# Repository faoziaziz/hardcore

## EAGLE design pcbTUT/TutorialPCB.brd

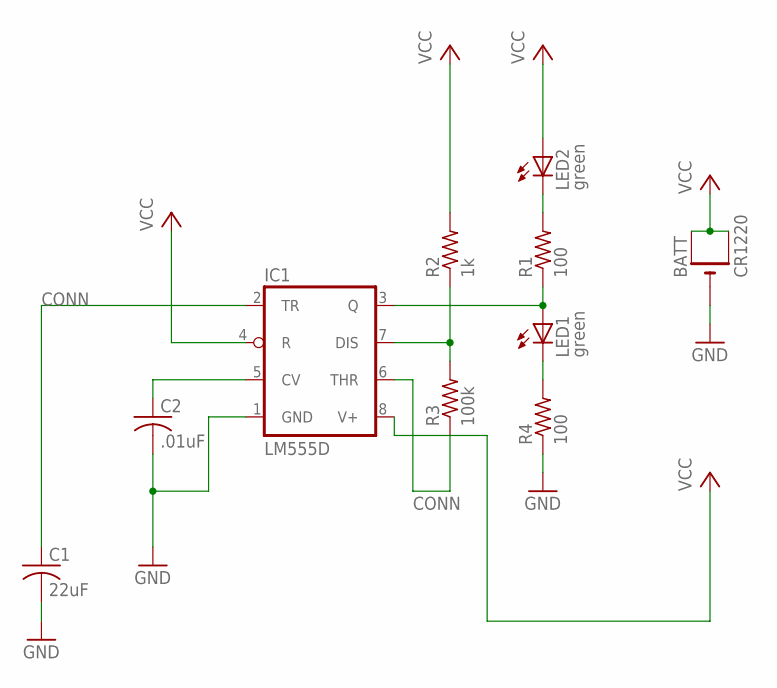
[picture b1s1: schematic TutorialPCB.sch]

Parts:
BATT: CR1220; CR1220-SMD
C1: 22uF; C0805
C2: .01uF; C0805
IC1: LM555D; SO08
LED1, LED2: green; CHIPLED_0805
R1, R4: 100; R0805
R2: 1k; R0805
R3: 100k; R0805

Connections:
CONN: C1.1, IC1.2 (TR), IC1.6 (THR), R3.1
GND: BATT.-, C1.2, C2.2, IC1.1 (GND), R4.1
unnamed: LED1.C, R4.2
unnamed: IC1.3 (Q), LED1.A, R1.1
unnamed: LED2.C, R1.2
unnamed: IC1.7 (DIS), R2.1, R3.2
unnamed: C2.1, IC1.5 (CV)
VCC: BATT.+$1 (+), BATT.+$2 (+1), IC1.4 (R), IC1.8 (V+), LED2.A, R2.2

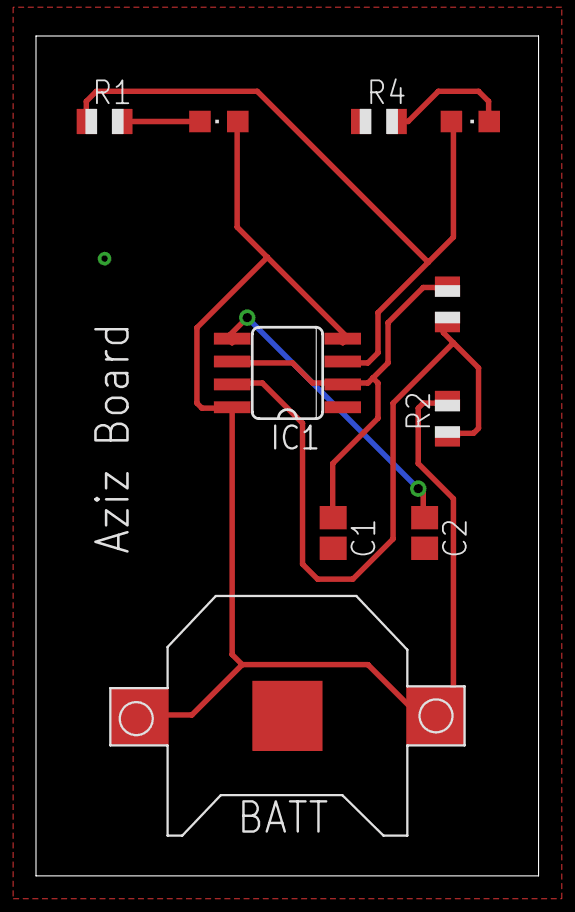
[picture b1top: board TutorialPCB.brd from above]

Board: 2 copper layers, 27.9 x 46.7 mm, 10 parts (0 on the bottom side), 8 nets.

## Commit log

2018-03-27 Aziz geker
